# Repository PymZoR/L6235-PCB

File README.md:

# L6235-PCB

Implements the "typical application" ([datasheet](./doc/datasheet.pdf)) as a single sided PCB.  

## Specifications

- Require a 5V logic supply voltage (LOGI1), as well as a power one (PWR1)
- 69.8*66mm. 4 M3 mounting holes
- Variable reference voltage as described in the ([application note](./doc/application_note.pdf)) through VREF pin (CMD1)

## Schematic

## PCB

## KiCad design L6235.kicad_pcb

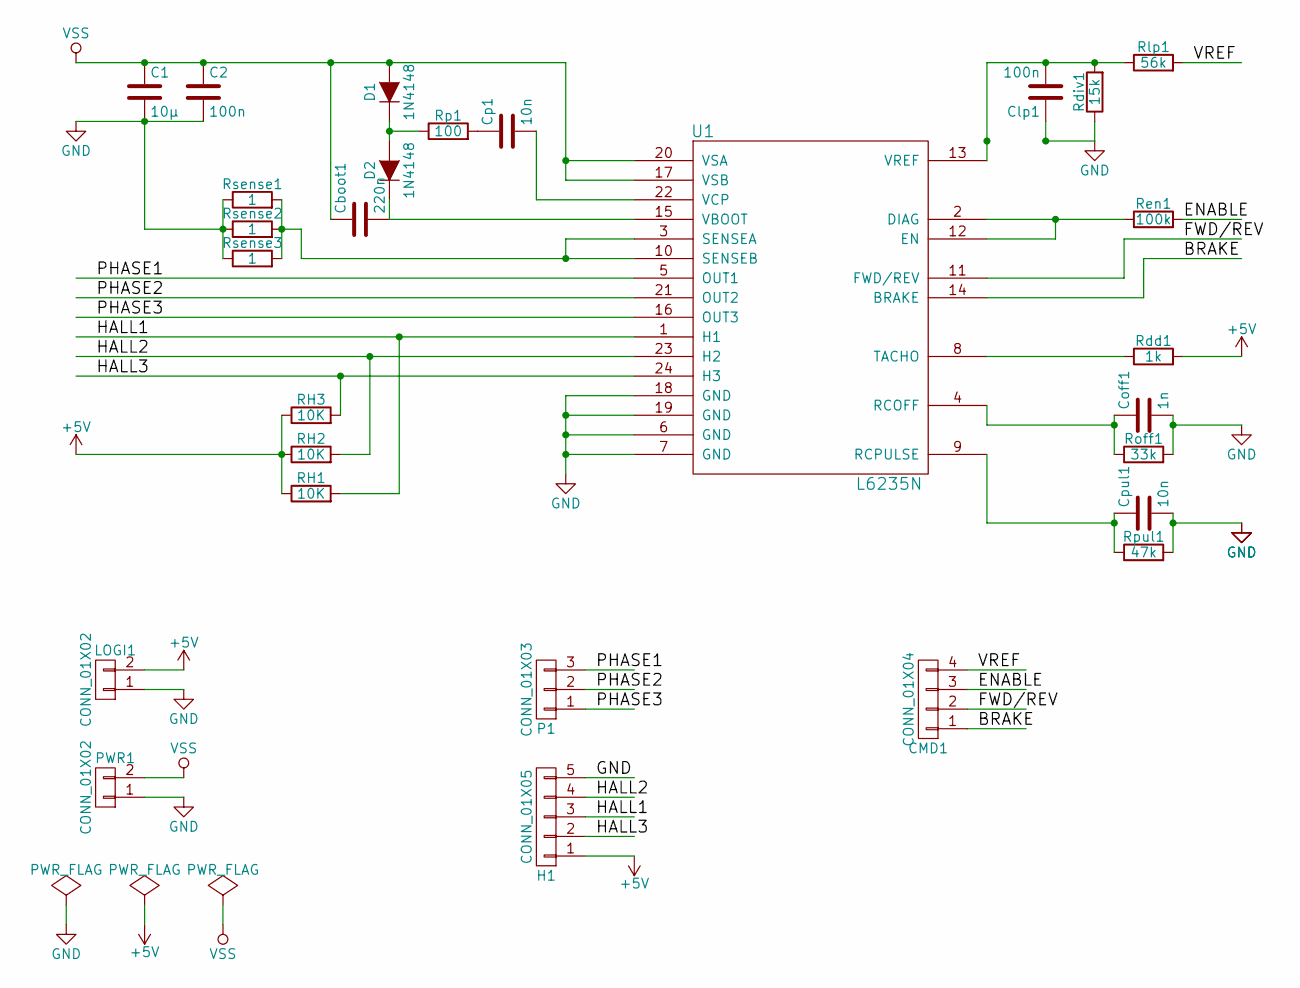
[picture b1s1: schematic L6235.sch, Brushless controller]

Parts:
C1: 10µ; C_Radial_D5_L11_P2
C2: 100n; C_Disc_D3_P2.5
CMD1: CONN_01X04; Socket_Strip_Straight_1x04
Cboot1: 220n; C_Radial_D5_L11_P2
Clp1: 100n; C_Disc_D3_P2.5
Coff1: 1n; C_Disc_D3_P2.5
Cp1: 10n; C_Disc_D3_P2.5
Cpul1: 10n; C_Disc_D3_P2.5
D1, D2: 1N4148; Diode_DO-35_SOD27_Horizontal_RM10
H1: CONN_01X05; Socket_Strip_Straight_1x05
LOGI1: CONN_01X02; Socket_Strip_Straight_1x02
P1: CONN_01X03; Socket_Strip_Straight_1x03
PWR1: CONN_01X02; bornier2
RH1, RH2, RH3: 10K; Resistor_Horizontal_RM10mm
Rdd1: 1k; Resistor_Horizontal_RM10mm
Rdiv1: 15k; Resistor_Horizontal_RM10mm
Ren1: 100k; Resistor_Horizontal_RM10mm
Rlp1: 56k; Resistor_Horizontal_RM10mm
Roff1: 33k; Resistor_Horizontal_RM10mm
Rp1: 100; Resistor_Horizontal_RM10mm
Rpul1: 47k; Resistor_Horizontal_RM10mm
Rsense1, Rsense2, Rsense3: 1; Resistor_Horizontal_RM10mm
U1: L6235N; DIP-24_W7.62mm

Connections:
+5V: H1.1, LOGI1.2, RH1.1, RH2.1, RH3.1, Rdd1.2
/BRAKE: CMD1.1, U1.14 (BRAKE)
/ENABLE: CMD1.3, Ren1.2
/FWD/REV: CMD1.2, U1.11 (FWD/REV)
/HALL1: H1.3, RH1.2, U1.1 (H1)
/HALL2: H1.4, RH2.2, U1.23 (H2)
/HALL3: H1.2, RH3.2, U1.24 (H3)
/PHASE1: P1.3, U1.5 (OUT1)
/PHASE2: P1.2, U1.21 (OUT2)
/PHASE3: P1.1, U1.16 (OUT3)
/VREF: CMD1.4, Rlp1.2
GND: C1.2, C2.2, Clp1.1, Coff1.2, Cpul1.2, H1.5, LOGI1.1, PWR1.1, Rdiv1.1, Roff1.2, Rpul1.2, Rsense1.1, Rsense2.1, Rsense3.1, U1.6 (GND), U1.7 (GND), U1.18 (GND), U1.19 (GND)
unnamed: Cboot1.2, D2.1 (K), U1.15 (VBOOT)
unnamed: Clp1.2, Rdiv1.2, Rlp1.1, U1.13 (VREF)
unnamed: Coff1.1, Roff1.1, U1.4 (RCOFF)
unnamed: Cp1.1, Rp1.2
unnamed: Cp1.2, U1.22 (VCP)
unnamed: Cpul1.1, Rpul1.1, U1.9 (RCPULSE)
unnamed: D1.1 (K), D2.2 (A), Rp1.1
unnamed: Rdd1.1, U1.8 (TACHO)
unnamed: Ren1.1, U1.2 (DIAG), U1.12 (EN)
unnamed: Rsense1.2, Rsense2.2, Rsense3.2, U1.3 (SENSEA), U1.10 (SENSEB)
VSS: C1.1, C2.1, Cboot1.1, D1.2 (A), PWR1.2, U1.17 (VSB), U1.20 (VSA)

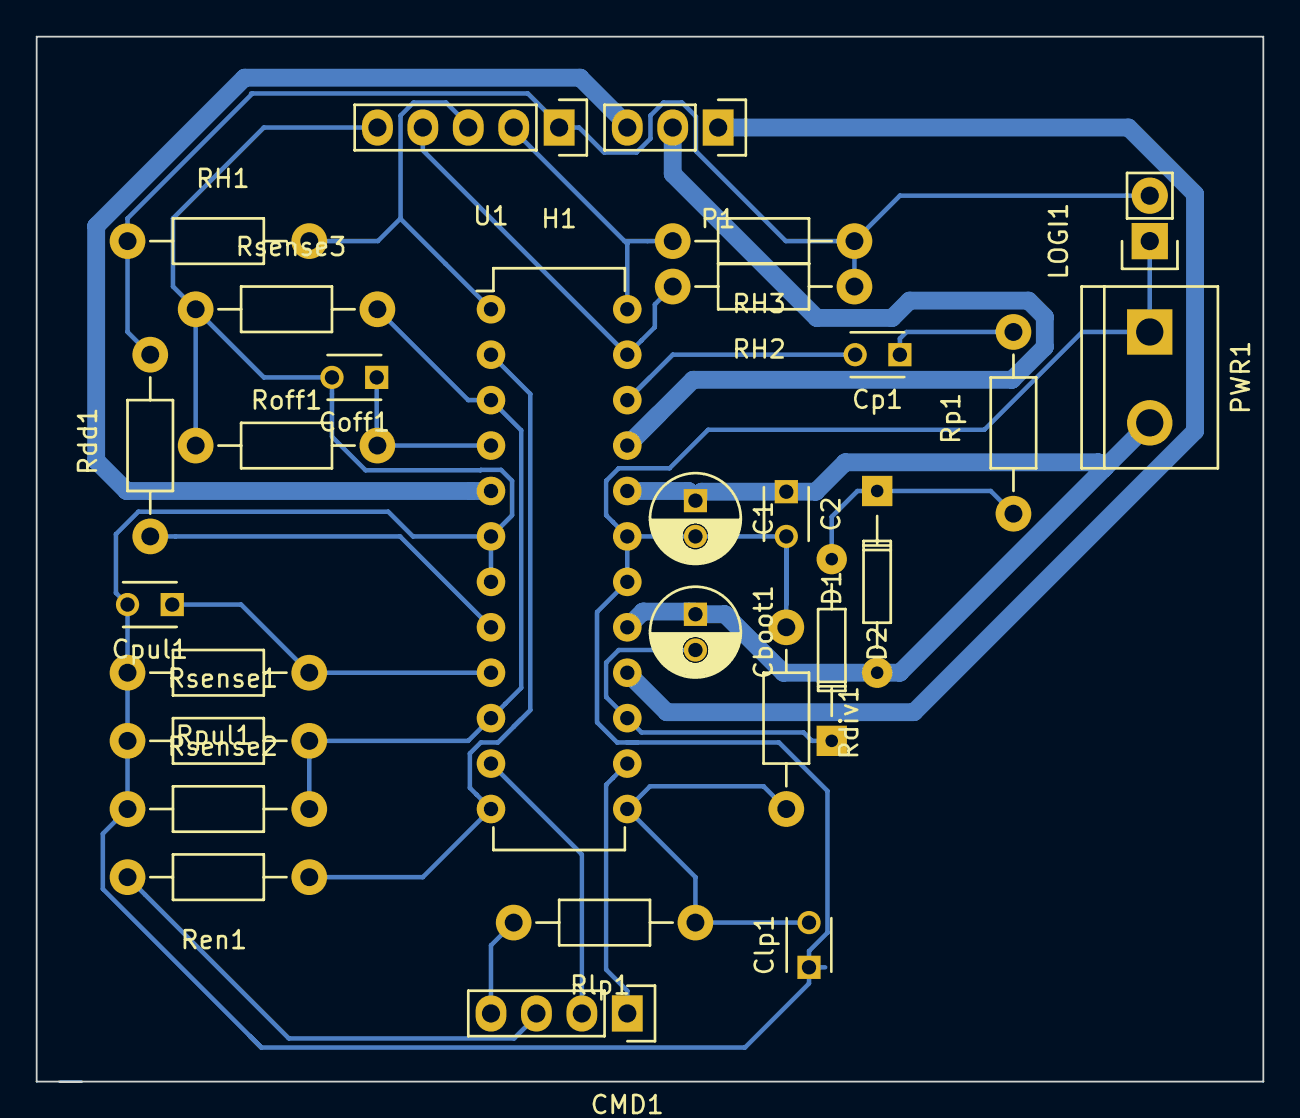
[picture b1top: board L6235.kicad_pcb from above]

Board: 2 copper layers, 68.6 x 58.4 mm, 28 parts (0 on the bottom side), 23 nets.

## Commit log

2016-07-23 Add OSX specific files to .gitignore
2016-07-23 Add schema, PCB and lib
2016-07-24 fix: larger GND plan next to Phase2
2016-07-24 feature: add mounting holes; fix: add GND bridge
2016-07-24 feature: add README
